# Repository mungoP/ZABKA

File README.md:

# Ż.A.B.K.A.

**Zero-moment Assisted Bipedal Kinetic Android**

ŻABKA ("little frog" in Polish) is a DIY 3D-printed humanoid robot. The current focus is the legs.

## Planned Specs

- **Height:** 3-4 ft
- **Legs:** 6 DoF each (3 hip, 1 knee, 2 ankle), 12 DoF total
- **Actuators:** Integrated motors with built-in drivers, controlled over CAN
- **Structure:** PETG, 4 walls, 10-20% infill
- **Power:** 48V Li-ion battery
- **Estimated weight:** 14-18 kg without arms

## Status

Early planning: selecting motors and finalizing the leg design.

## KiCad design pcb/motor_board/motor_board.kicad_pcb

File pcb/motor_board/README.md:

# Motor Board Planned Components

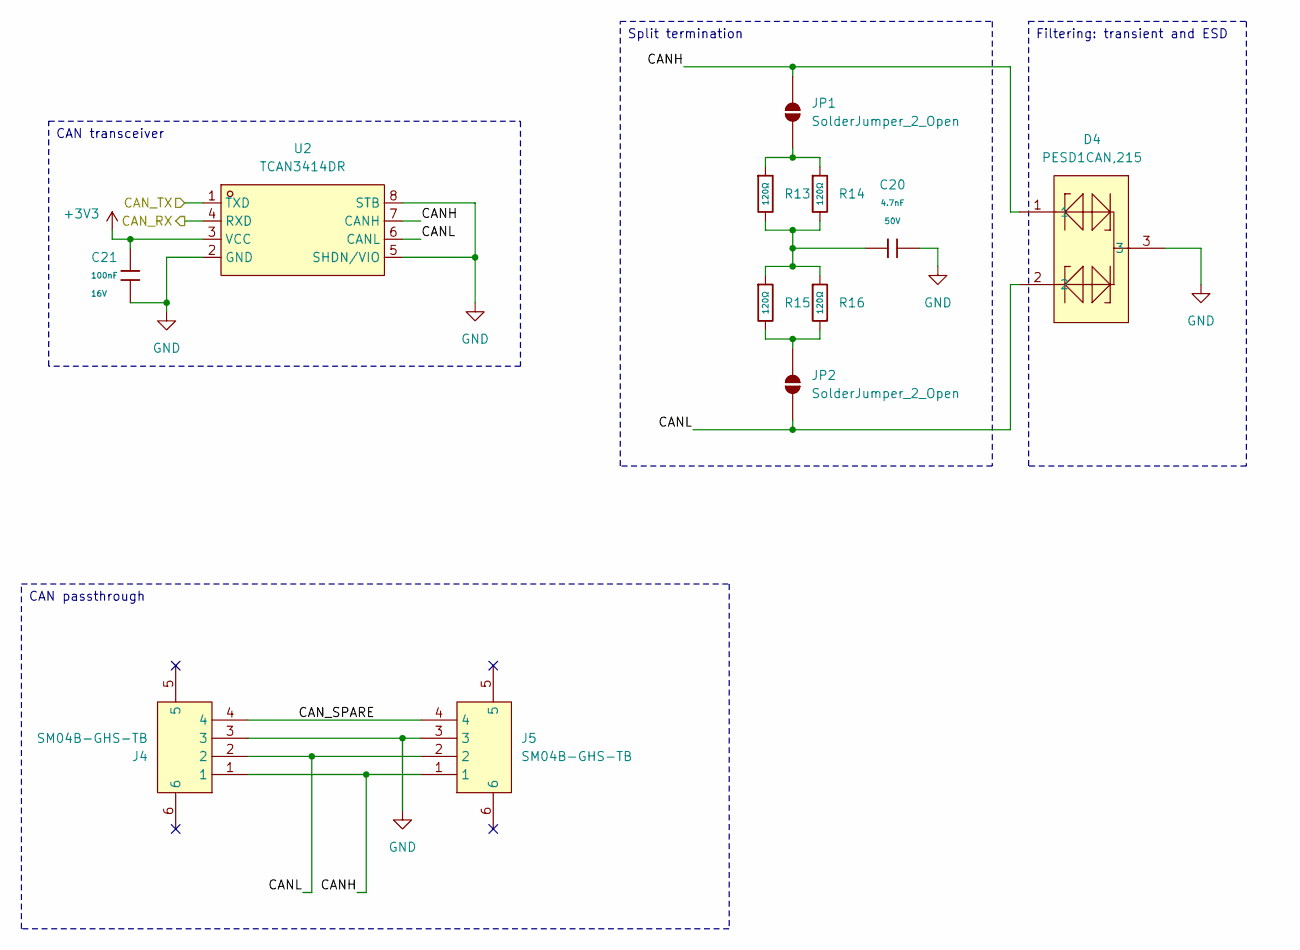
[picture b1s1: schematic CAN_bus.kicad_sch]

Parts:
C20: 4.7nF; C_0402; Voltage Rated 50V; Tolerance ±10%; Part 0402B472K500NT; LCSC C1538
C21: 100nF; C_0402; Voltage Rated 16V; Tolerance ±10%; Part CL05B104KO5NNNC; LCSC C1525
D4: PESD1CAN,215; SOT-23_L2.9-W1.3-P1.90-LS2.4-BR; MPN PESD1CAN,215; LCSC Part C15771
J4, J5: SM04B-GHS-TB; CONN-SMD_4P-P1.25_SM04B-GHS-TB-LF-SN; MPN SM04B-GHS-TB(LF)(SN); LCSC Part C189895
JP1, JP2: SolderJumper_2_Open; SolderJumper-2_P1.3mm_Open_Pad1.0x1.5mm
R13, R14, R15, R16: 120Ω; R_0402; Overload Voltage (Max) 50V; Tolerance ±1%; Part 0402WGF1200TCE; LCSC C25079
U2: TCAN3414DR; SOIC-8_L4.9-W3.9-P1.27-LS6.0-BL; MPN TCAN3414DR; LCSC Part C22396693

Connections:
+3V3: C21.1, U2.3 (VCC); also elsewhere on the board
/CAN bus/CANH: D4.1, J4.1, J5.1, JP1.2 (B), U2.7 (CANH)
/CAN bus/CANL: D4.2, J4.2, J5.2, JP2.1 (A), U2.6 (CANL)
/CAN bus/CAN_RX: U2.4 (RXD); also elsewhere on the board
/CAN bus/CAN_SPARE: J4.4, J5.4
/CAN bus/CAN_TX: U2.1 (TXD); also elsewhere on the board
GND: C20.2, C21.2, D4.3, J4.3, J5.3, U2.2 (GND), U2.5 (SHDN/VIO), U2.8 (STB); also elsewhere on the board
unnamed: C20.1, R13.2, R14.2, R15.1, R16.1
unnamed: JP1.1 (A), R13.1, R14.1
unnamed: JP2.2 (B), R15.2, R16.2

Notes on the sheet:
Split termination
CAN transceiver
CAN passthrough
Filtering: transient and ESD

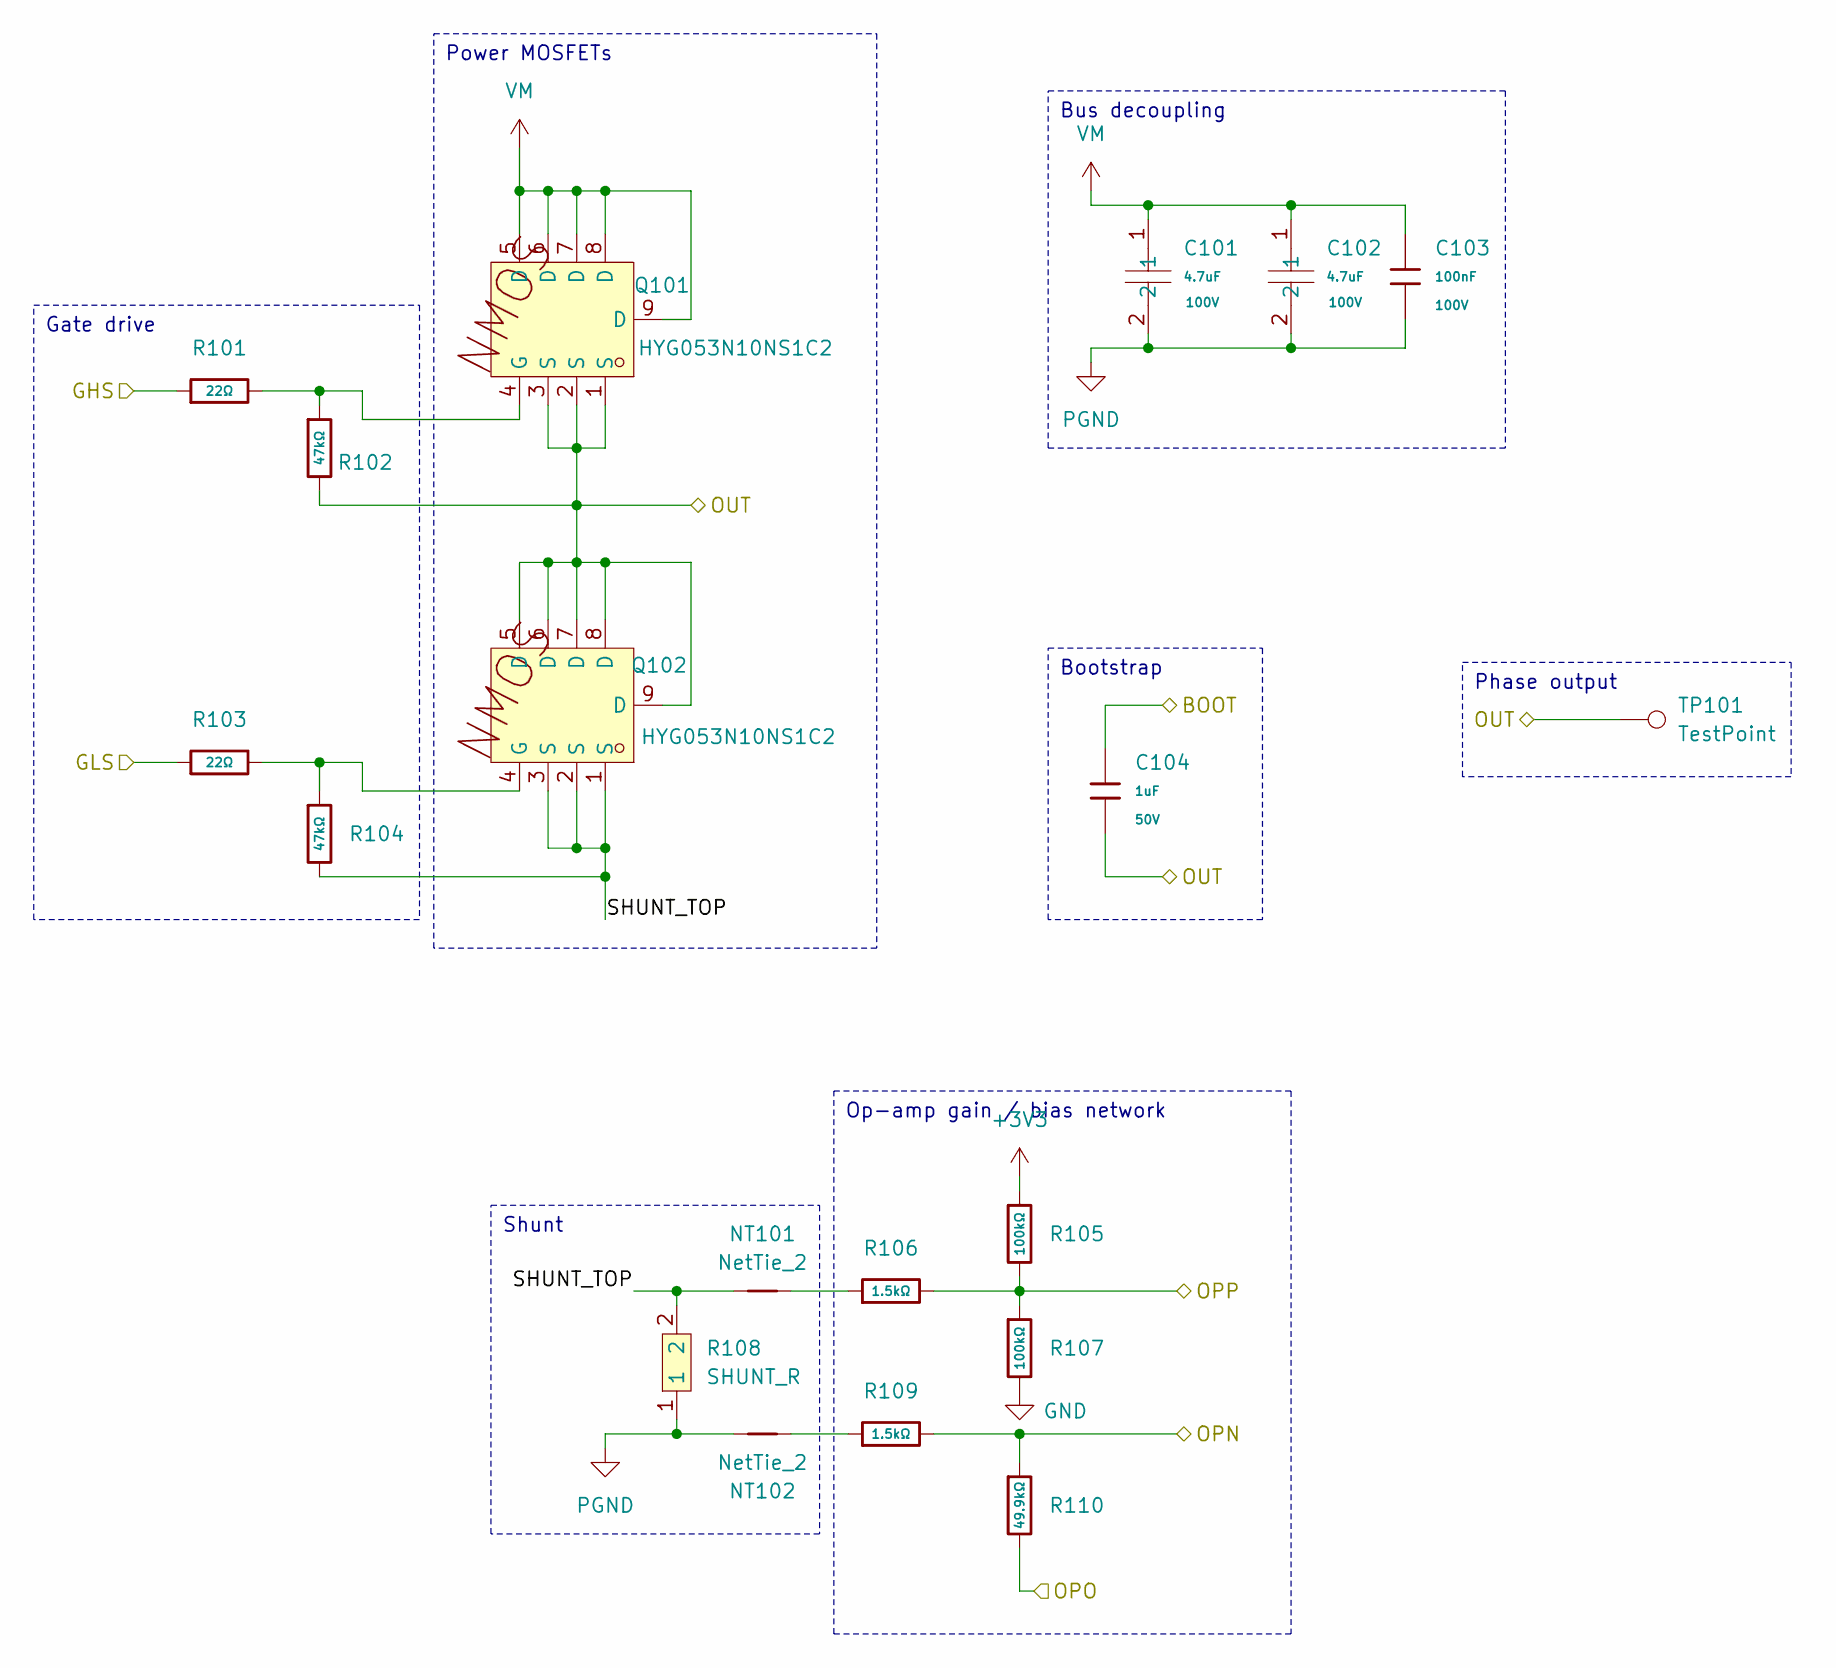
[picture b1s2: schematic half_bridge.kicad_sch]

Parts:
C101, C102: 4.7uF; C1210; MPN C1210X475K101T; LCSC Part C337978
C103: 100nF; C_0805; Voltage Rated 100V; Tolerance ±10%; Part CL21B104KCFNNNE; LCSC C28233
C104: 1uF; C_0603; Voltage Rated 50V; Tolerance ±10%; Part CL10A105KB8NNNC; LCSC C15849
NT101, NT102: NetTie_2; NetTie-2_SMD_Pad0.5mm
Q101, Q102: HYG053N10NS1C2; PDFN-8_L5.8-W5.0-P1.27-LS6.2-BL; MPN HYG053N10NS1C2; LCSC Part C2986239
R101, R103: 22Ω; R_0603; Overload Voltage (Max) 75V; Tolerance ±1%; Part 0603WAF220JT5E; LCSC C23345
R102, R104: 47kΩ; R_0402; Overload Voltage (Max) 50V; Tolerance ±1%; Part 0402WGF4702TCE; LCSC C25792
R105, R107: 100kΩ; R_0603; Overload Voltage (Max) 75V; Tolerance ±1%; Part 0603WAF1003T5E; LCSC C25803
R106, R109: 1.5kΩ; R_0603; Overload Voltage (Max) 75V; Tolerance ±1%; Part 0603WAF1501T5E; LCSC C22843
R108: SHUNT_R; RES-SMD_L6.4-W3.2_LR2512D-3W-1MR; MPN LR2512D-3W-1mR-1%; LCSC Part C500734
R110: 49.9kΩ; R_0402; Overload Voltage (Max) 50V; Tolerance ±1%; Part 0402WGF4992TCE; LCSC C25897
TP101: TestPoint; TestPoint_Pad_4.0x4.0mm

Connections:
+3V3: R105.1; also elsewhere on the board
/Controller/BOOT1: C104.1; also elsewhere on the board
/Controller/GHS1: R101.1; also elsewhere on the board
/Controller/GLS1: R103.1; also elsewhere on the board
/Controller/OPN1: R109.2, R110.1; also elsewhere on the board
/Controller/OPO1: R110.2; also elsewhere on the board
/Controller/OPP1: R105.2, R106.2, R107.1; also elsewhere on the board
/Controller/OUT1: C104.2, Q101.1 (S), Q101.2 (S), Q101.3 (S), Q102.5 (D), Q102.6 (D), Q102.7 (D), Q102.8 (D), Q102.9 (D), R102.2, TP101.1 (1_1); also elsewhere on the board
/Half bridge - U/SHUNT_TOP: NT101.1, Q102.1 (S), Q102.2 (S), Q102.3 (S), R104.2, R108.2
GND: R107.2; also elsewhere on the board
unnamed: NT101.2, R106.1
unnamed: NT102.1, R109.1
unnamed: Q101.4 (G), R101.2, R102.1
unnamed: Q102.4 (G), R103.2, R104.1
PGND: C101.2, C102.2, C103.2, NT102.2, R108.1; also elsewhere on the board
VM: C101.1, C102.1, C103.1, Q101.5 (D), Q101.6 (D), Q101.7 (D), Q101.8 (D), Q101.9 (D); also elsewhere on the board

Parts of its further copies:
C201, C202, C301, C302: 4.7uF; C1210; MPN C1210X475K101T; LCSC Part C337978
C203, C303: 100nF; C_0805; Voltage Rated 100V; Tolerance ±10%; Part CL21B104KCFNNNE; LCSC C28233
C204, C304: 1uF; C_0603; Voltage Rated 50V; Tolerance ±10%; Part CL10A105KB8NNNC; LCSC C15849
NT201, NT202, NT301, NT302: NetTie_2; NetTie-2_SMD_Pad0.5mm
Q201, Q202, Q301, Q302: HYG053N10NS1C2; PDFN-8_L5.8-W5.0-P1.27-LS6.2-BL; MPN HYG053N10NS1C2; LCSC Part C2986239
R201, R203, R301, R303: 22Ω; R_0603; Overload Voltage (Max) 75V; Tolerance ±1%; Part 0603WAF220JT5E; LCSC C23345
R202, R204, R302, R304: 47kΩ; R_0402; Overload Voltage (Max) 50V; Tolerance ±1%; Part 0402WGF4702TCE; LCSC C25792
R205, R207, R305, R307: 100kΩ; R_0603; Overload Voltage (Max) 75V; Tolerance ±1%; Part 0603WAF1003T5E; LCSC C25803
R206, R209, R306, R309: 1.5kΩ; R_0603; Overload Voltage (Max) 75V; Tolerance ±1%; Part 0603WAF1501T5E; LCSC C22843
R208, R308: SHUNT_R; RES-SMD_L6.4-W3.2_LR2512D-3W-1MR; MPN LR2512D-3W-1mR-1%; LCSC Part C500734
R210, R310: 49.9kΩ; R_0402; Overload Voltage (Max) 50V; Tolerance ±1%; Part 0402WGF4992TCE; LCSC C25897
TP201, TP301: TestPoint; TestPoint_Pad_4.0x4.0mm

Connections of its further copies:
+3V3: R205.1, R305.1; also elsewhere on the board
/Controller/BOOT2: C204.1; also elsewhere on the board
/Controller/BOOT3: C304.1; also elsewhere on the board
/Controller/GHS2: R201.1; also elsewhere on the board
/Controller/GHS3: R301.1; also elsewhere on the board
/Controller/GLS2: R203.1; also elsewhere on the board
/Controller/GLS3: R303.1; also elsewhere on the board
/Controller/OPN2: R209.2, R210.1; also elsewhere on the board
/Controller/OPN3: R309.2, R310.1; also elsewhere on the board
/Controller/OPO2: R210.2; also elsewhere on the board
/Controller/OPO3: R310.2; also elsewhere on the board
/Controller/OPP2: R205.2, R206.2, R207.1; also elsewhere on the board
/Controller/OPP3: R305.2, R306.2, R307.1; also elsewhere on the board
/Controller/OUT2: C204.2, Q201.1 (S), Q201.2 (S), Q201.3 (S), Q202.5 (D), Q202.6 (D), Q202.7 (D), Q202.8 (D), Q202.9 (D), R202.2, TP201.1 (1_1); also elsewhere on the board
/Controller/OUT3: C304.2, Q301.1 (S), Q301.2 (S), Q301.3 (S), Q302.5 (D), Q302.6 (D), Q302.7 (D), Q302.8 (D), Q302.9 (D), R302.2, TP301.1 (1_1); also elsewhere on the board
/Half bridge - V/SHUNT_TOP: NT201.1, Q202.1 (S), Q202.2 (S), Q202.3 (S), R204.2, R208.2
/Half bridge - W/SHUNT_TOP: NT301.1, Q302.1 (S), Q302.2 (S), Q302.3 (S), R304.2, R308.2
GND: R207.2, R307.2; also elsewhere on the board
unnamed: NT201.2, R206.1
unnamed: NT202.1, R209.1
unnamed: NT301.2, R306.1
unnamed: NT302.1, R309.1
unnamed: Q201.4 (G), R201.2, R202.1
unnamed: Q202.4 (G), R203.2, R204.1
unnamed: Q301.4 (G), R301.2, R302.1
unnamed: Q302.4 (G), R303.2, R304.1
PGND: C201.2, C202.2, C203.2, C301.2, C302.2, C303.2, NT202.2, NT302.2, R208.1, R308.1; also elsewhere on the board
VM: C201.1, C202.1, C203.1, C301.1, C302.1, C303.1, Q201.5 (D), Q201.6 (D), Q201.7 (D), Q201.8 (D), Q201.9 (D), Q301.5 (D), Q301.6 (D), Q301.7 (D), Q301.8 (D), Q301.9 (D); also elsewhere on the board

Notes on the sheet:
Bootstrap
Gate drive
Shunt
Bus decoupling
Power MOSFETs
Op-amp gain / bias network
Phase output

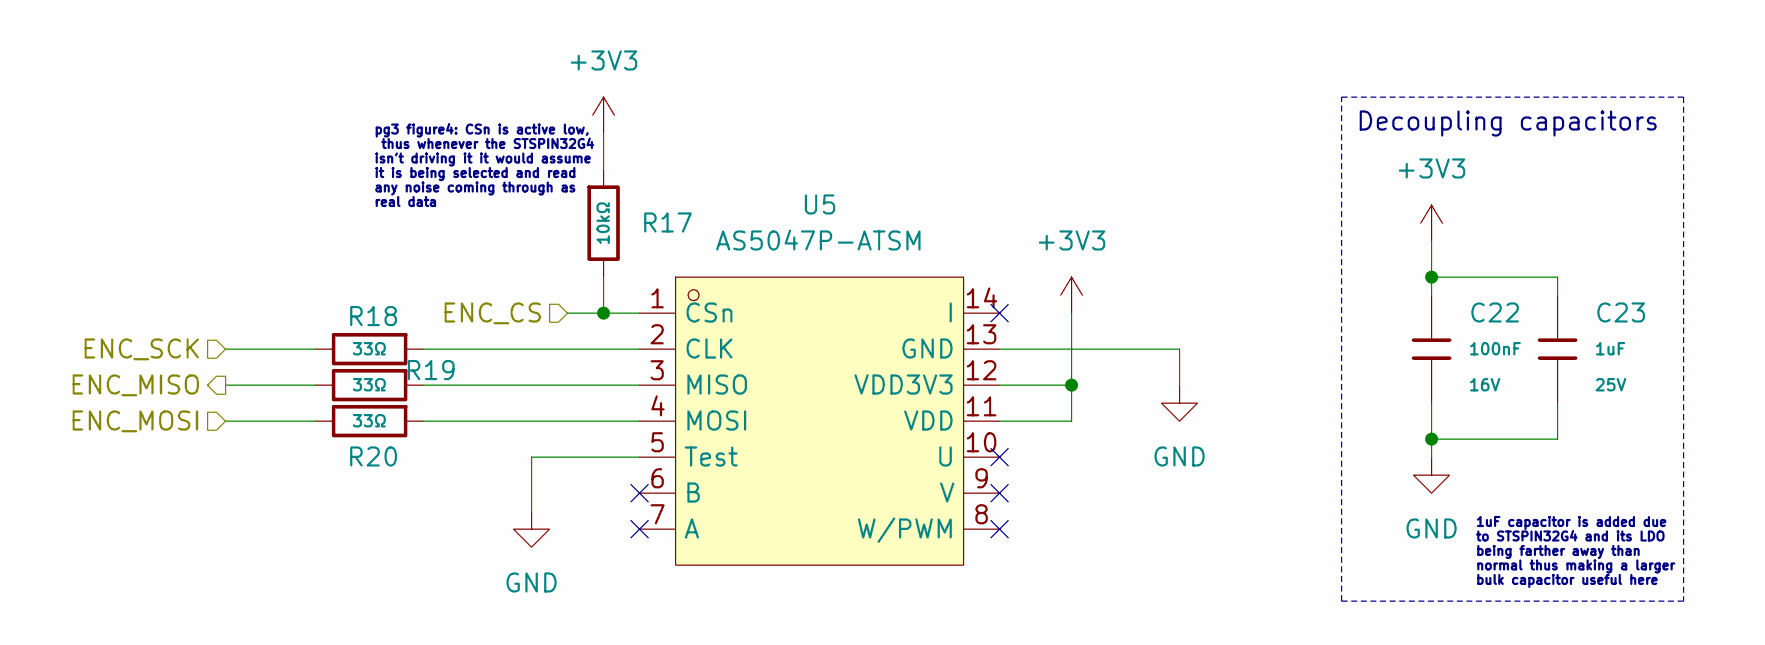
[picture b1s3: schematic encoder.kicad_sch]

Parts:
C22: 100nF; C_0402; Voltage Rated 16V; Tolerance ±10%; Part CL05B104KO5NNNC; LCSC C1525
C23: 1uF; C_0402; Voltage Rated 25V; Tolerance ±10%; Part CL05A105KA5NQNC; LCSC C52923
R17: 10kΩ; R_0402; Overload Voltage (Max) 50V; Tolerance ±1%; Part 0402WGF1002TCE; LCSC C25744
R18, R19, R20: 33Ω; R_0402; Overload Voltage (Max) 50V; Tolerance ±1%; Part 0402WGF330JTCE; LCSC C25105
U5: AS5047P-ATSM; TSSOP-14_L5.0-W4.4-P0.65-LS6.4-BL; MPN AS5047P-ATSM; LCSC Part C962063

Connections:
+3V3: C22.1, C23.1, R17.1, U5.11 (VDD), U5.12 (VDD3V3); also elsewhere on the board
/Controller/ENC_CS: R17.2, U5.1 (CSn); also elsewhere on the board
/Controller/ENC_MISO: R19.2; also elsewhere on the board
/Controller/ENC_MOSI: R20.2; also elsewhere on the board
/Controller/ENC_SCK: R18.2; also elsewhere on the board
GND: C22.2, C23.2, U5.5 (Test), U5.13 (GND); also elsewhere on the board
unnamed: R18.1, U5.2 (CLK)
unnamed: R19.1, U5.3 (MISO)
unnamed: R20.1, U5.4 (MOSI)

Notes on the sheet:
pg3 figure4: CSn is active low, thus whenever the STSPIN32G4 isn't driving it it would assume it is being selected and read any noise coming through as real data
1uF capacitor is added due to STSPIN32G4 and its LDO being farther away than normal thus making a larger bulk capacitor useful here
Decoupling capacitors

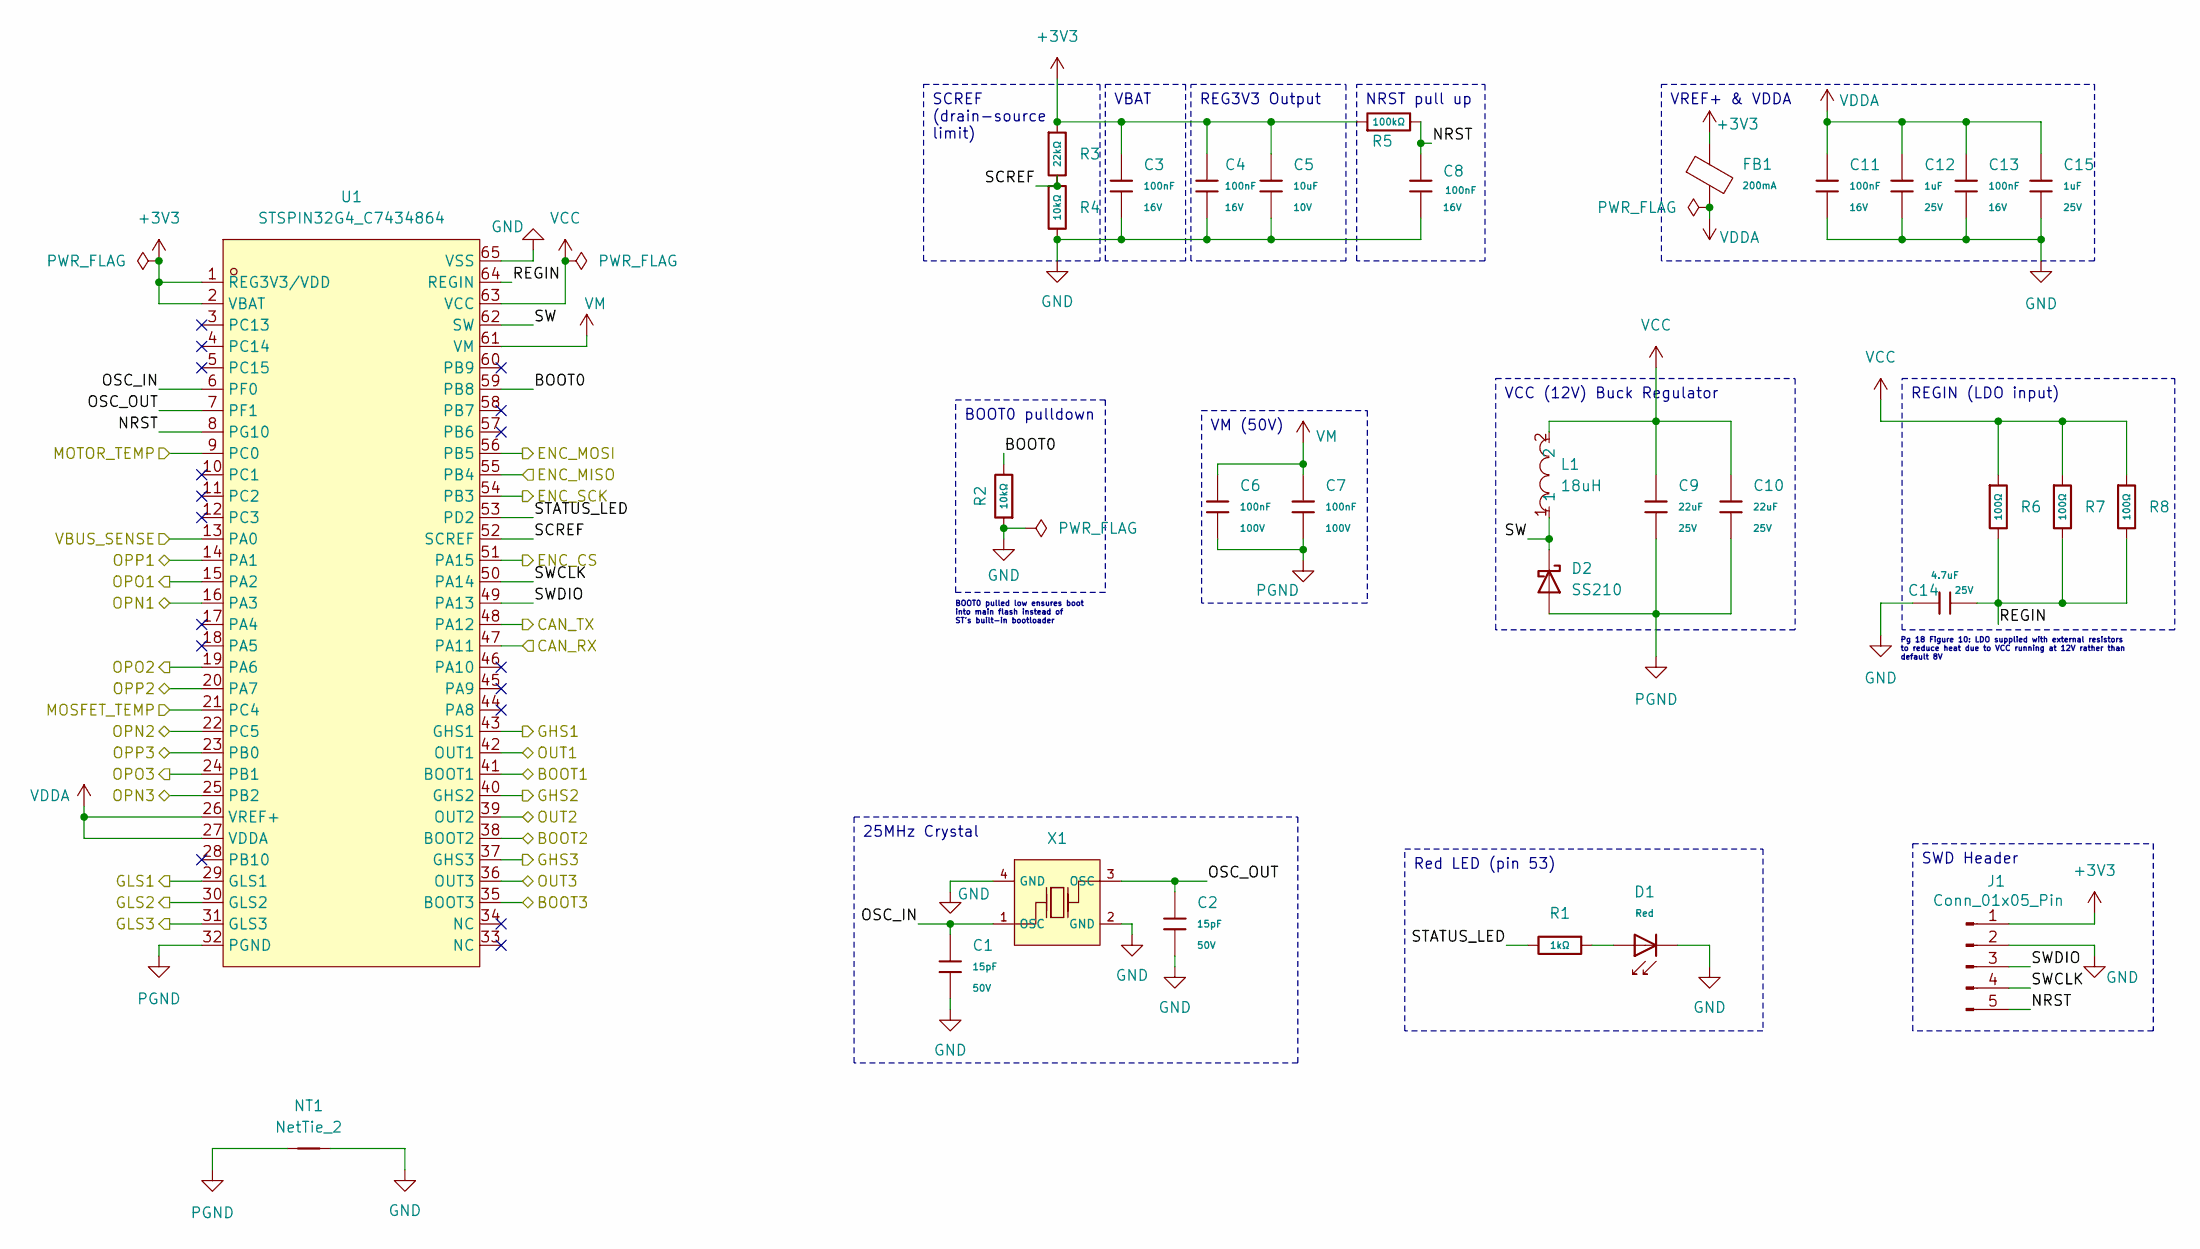
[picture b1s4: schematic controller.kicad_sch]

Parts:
C1, C2: 15pF; C_0402; Voltage Rated 50V; Tolerance ±5%; Part 0402CG150J500NT; LCSC C1548
C3, C4, C8, C11, C13: 100nF; C_0402; Voltage Rated 16V; Tolerance ±10%; Part CL05B104KO5NNNC; LCSC C1525
C5: 10uF; C_0603; Voltage Rated 10V; Tolerance ±10%; Part CL10A106KP8NNNC; LCSC C19702
C6, C7: 100nF; C_0805; Voltage Rated 100V; Tolerance ±10%; Part CL21B104KCFNNNE; LCSC C28233
C9, C10: 22uF; C_1206; Voltage Rated 25V; Tolerance ±10%; Part CL31A226KAHNNNE; LCSC C12891
C12, C15: 1uF; C_0402; Voltage Rated 25V; Tolerance ±10%; Part CL05A105KA5NQNC; LCSC C52923
C14: 4.7uF; C_0805; Voltage Rated 25V; Tolerance ±10%; Part CL21A475KAQNNNE; LCSC C1779
D1: Red; D_0603; Part KT-0603R; LCSC C2286
D2: SS210; D_SMA
FB1: FB_0603; Current Rating 200mA; Tolerance ±25%; Part GZ1608D601TF; LCSC C1002
J1: Conn_01x05_Pin; PinHeader_1x05_P2.54mm_Horizontal
L1: 18uH; IND-SMD_L6.0-W6.0_FNR60XXS; MPN FNR6020S180MT; LCSC Part C168016
NT1: NetTie_2; NetTie-2_SMD_Pad0.5mm
R1: 1kΩ; R_0402; Overload Voltage (Max) 50V; Tolerance ±1%; Part 0402WGF1001TCE; LCSC C11702
R2, R4: 10kΩ; R_0402; Overload Voltage (Max) 50V; Tolerance ±1%; Part 0402WGF1002TCE; LCSC C25744
R3: 22kΩ; R_0402; Overload Voltage (Max) 50V; Tolerance ±1%; Part 0402WGF2202TCE; LCSC C25768
R5: 100kΩ; R_0402; Overload Voltage (Max) 50V; Tolerance ±1%; Part 0402WGF1003TCE; LCSC C25741
R6, R7, R8: 100Ω; R_1206; Overload Voltage (Max) 200V; Tolerance ±1%; Part 1206W4F1000T5E; LCSC C17901
U1: STSPIN32G4_C7434864; VFQFPN-64_L9.0-W9.0-P0.50-TL-EP4.0; MPN STSPIN32G4; LCSC Part C7434864
X1: X322525MOB4SI; OSC-SMD_4P-L3.2-W2.5-BL; Frequency Tolerance ±10ppm; Part X322525MOB4SI; LCSC C9006

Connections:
+3V3: C3.1, C4.1, C5.1, FB1.1, J1.1, R3.1, R5.1, U1.1 (REG3V3/VDD), U1.2 (VBAT); also elsewhere on the board
/CAN bus/CAN_RX: U1.47 (PA11); also elsewhere on the board
/CAN bus/CAN_TX: U1.48 (PA12); also elsewhere on the board
/Controller/BOOT0: R2.2, U1.59 (PB8)
/Controller/BOOT1: U1.41 (BOOT1); also elsewhere on the board
/Controller/BOOT2: U1.38 (BOOT2); also elsewhere on the board
/Controller/BOOT3: U1.35 (BOOT3); also elsewhere on the board
/Controller/ENC_CS: U1.51 (PA15); also elsewhere on the board
/Controller/ENC_MISO: U1.55 (PB4); also elsewhere on the board
/Controller/ENC_MOSI: U1.56 (PB5); also elsewhere on the board
/Controller/ENC_SCK: U1.54 (PB3); also elsewhere on the board
/Controller/GHS1: U1.43 (GHS1); also elsewhere on the board
/Controller/GHS2: U1.40 (GHS2); also elsewhere on the board
/Controller/GHS3: U1.37 (GHS3); also elsewhere on the board
/Controller/GLS1: U1.29 (GLS1); also elsewhere on the board
/Controller/GLS2: U1.30 (GLS2); also elsewhere on the board
/Controller/GLS3: U1.31 (GLS3); also elsewhere on the board
/Controller/MOSFET_TEMP: U1.21 (PC4); also elsewhere on the board
/Controller/MOTOR_TEMP: U1.9 (PC0); also elsewhere on the board
/Controller/NRST: C8.1, J1.5, R5.2, U1.8 (PG10)
/Controller/OPN1: U1.16 (PA3); also elsewhere on the board
/Controller/OPN2: U1.22 (PC5); also elsewhere on the board
/Controller/OPN3: U1.25 (PB2); also elsewhere on the board
/Controller/OPO1: U1.15 (PA2); also elsewhere on the board
/Controller/OPO2: U1.19 (PA6); also elsewhere on the board
/Controller/OPO3: U1.24 (PB1); also elsewhere on the board
/Controller/OPP1: U1.14 (PA1); also elsewhere on the board
/Controller/OPP2: U1.20 (PA7); also elsewhere on the board
/Controller/OPP3: U1.23 (PB0); also elsewhere on the board
/Controller/OSC_IN: C1.1, U1.6 (PF0), X1.1 (OSC)
/Controller/OSC_OUT: C2.1, U1.7 (PF1), X1.3 (OSC)
/Controller/OUT1: U1.42 (OUT1); also elsewhere on the board
/Controller/OUT2: U1.39 (OUT2); also elsewhere on the board
/Controller/OUT3: U1.36 (OUT3); also elsewhere on the board
/Controller/REGIN: C14.2, R6.2, R7.2, R8.2, U1.64 (REGIN)
/Controller/SCREF: R3.2, R4.1, U1.52 (SCREF)
/Controller/STATUS_LED: R1.2, U1.53 (PD2)
/Controller/SW: D2.1 (K), L1.1, U1.62 (SW)
/Controller/SWCLK: J1.4, U1.50 (PA14)
/Controller/SWDIO: J1.3, U1.49 (PA13)
/Controller/VBUS_SENSE: U1.13 (PA0); also elsewhere on the board
GND: C1.2, C2.2, C3.2, C4.2, C5.2, C8.2, C11.2, C12.2, C13.2, C14.1, C15.2, D1.1, J1.2, NT1.2, R2.1, R4.2, U1.65 (VSS), X1.2 (GND), X1.4 (GND); also elsewhere on the board
unnamed: D1.2, R1.1
PGND: C6.2, C7.2, C9.2, C10.2, D2.2 (A), NT1.1, U1.32 (PGND); also elsewhere on the board
VCC: C9.1, C10.1, L1.2, R6.1, R7.1, R8.1, U1.63 (VCC)
VDDA: C11.1, C12.1, C13.1, C15.1, FB1.2, U1.26 (VREF+), U1.27 (VDDA)
VM: C6.1, C7.1, U1.61 (VM); also elsewhere on the board

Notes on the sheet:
Pg 18 Figure 10: LDO supplied with external resistors to reduce heat due to VCC running at 12V rather than default 8V
BOOT0 pulled low ensures boot into main flash instead of ST's built-in bootloader
Red LED (pin 53)
BOOT0 pulldown
SCREF (drain-source limit)
25MHz Crystal
NRST pull up
REG3V3 Output
VM (50V)
VCC (12V) Buck Regulator
VREF+ & VDDA
SWD Header
VBAT
REGIN (LDO input)

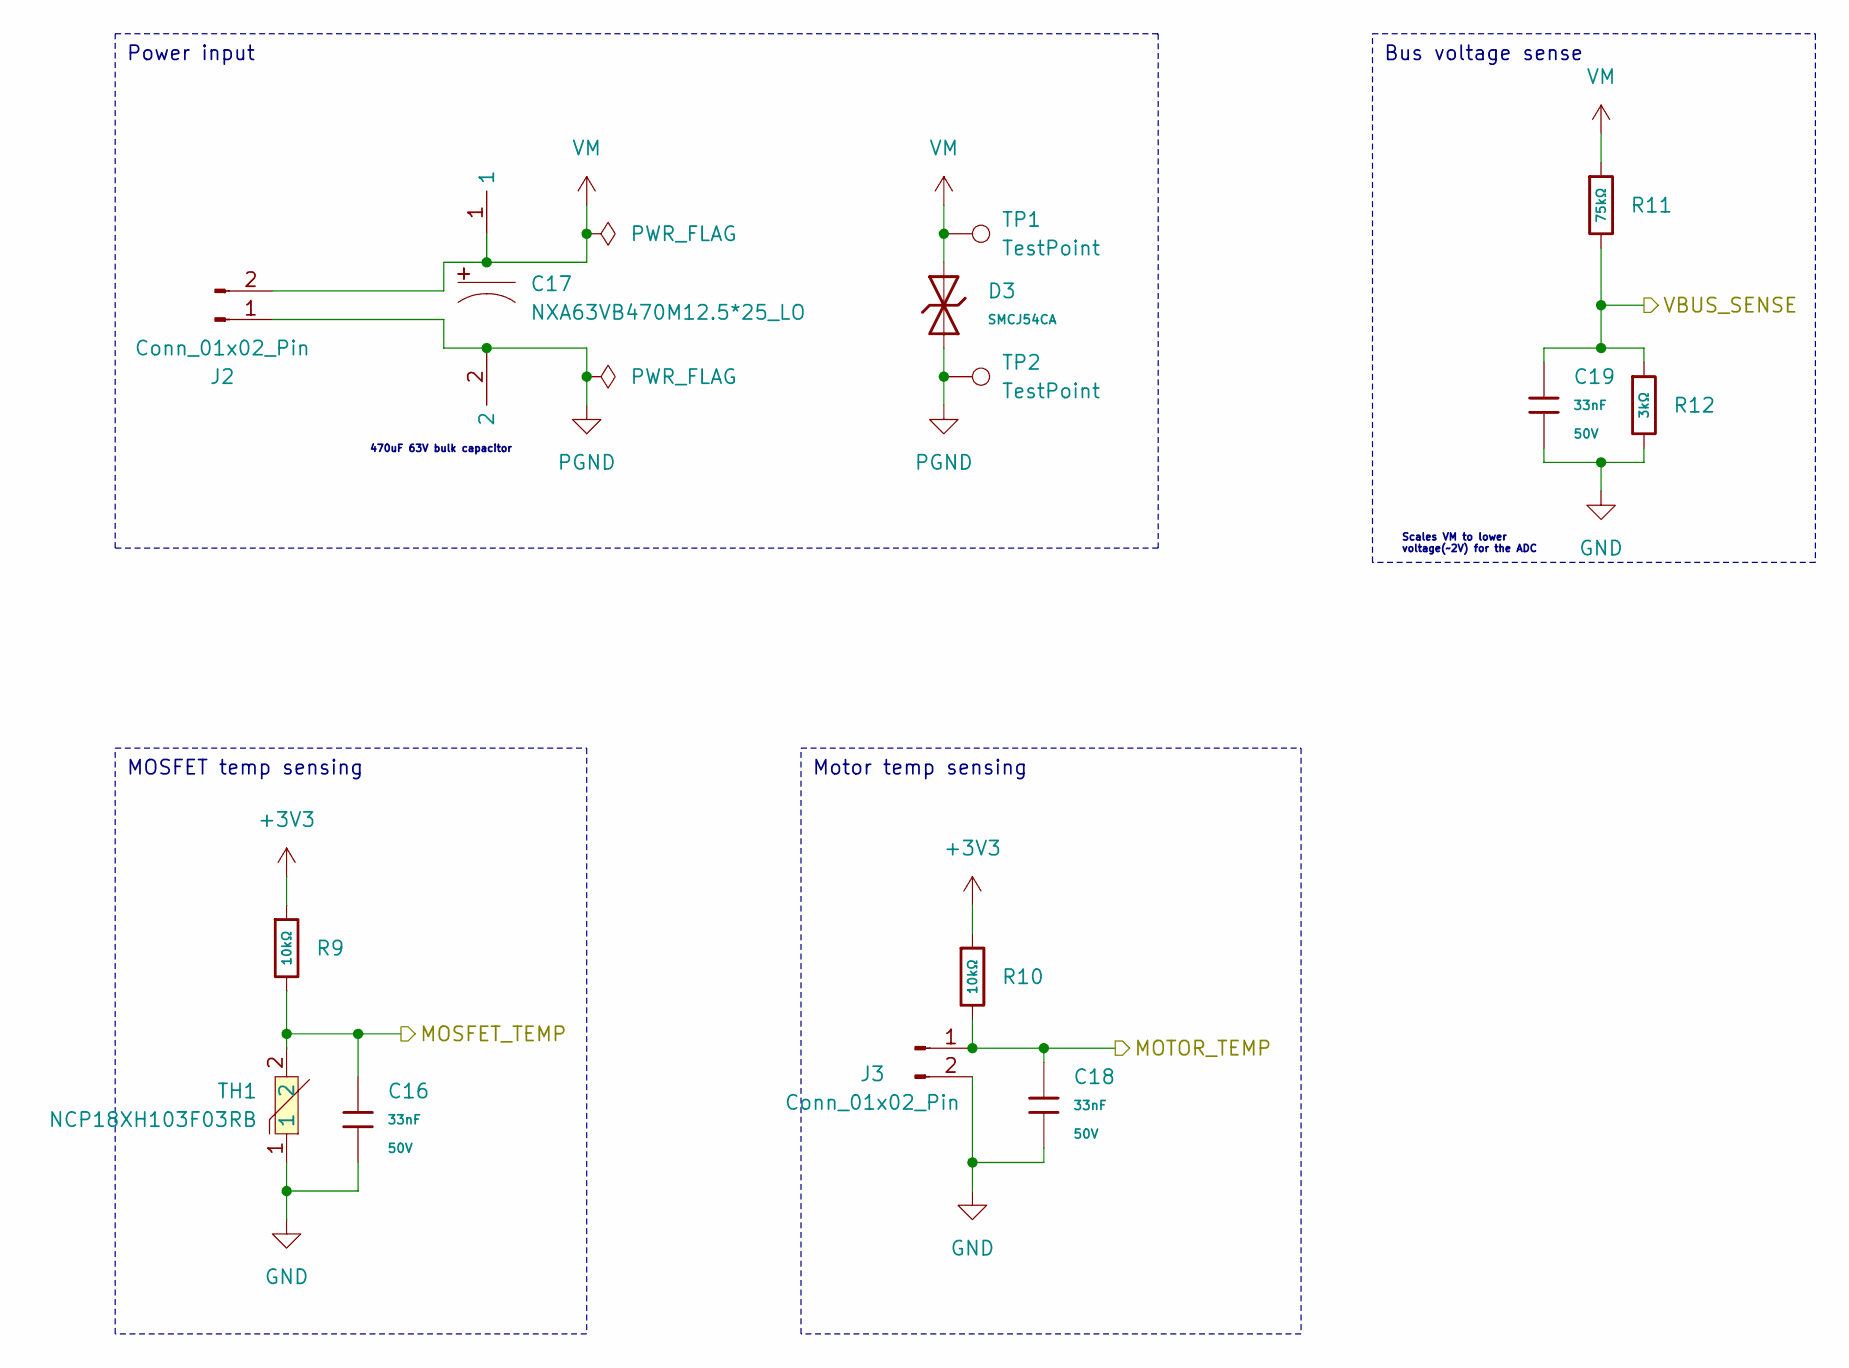
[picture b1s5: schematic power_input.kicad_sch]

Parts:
C16, C18, C19: 33nF; C_0603; Voltage Rated 50V; Tolerance ±10%; Part CL10B333KB8NNNC; LCSC C21117
C17: NXA63VB470M12.5*25_LO; CAP-TH_BD12.5-P5.00-D0.6-FD; MPN NXA63V470M12.5*25 LO; LCSC Part C371297
D3: SMCJ54CA; D_SMC; Clamping Voltage 87.1V; Voltage - Breakdown 66.3V; Part SMCJ54CA; LCSC C41411761
J2: Conn_01x02_Pin; AMASS_XT30PW-M_1x02_P2.50mm_Horizontal
J3: Conn_01x02_Pin; JST_GH_SM02B-GHS-TB_1x02-1MP_P1.25mm_Horizontal
R9, R10: 10kΩ; R_0402; Overload Voltage (Max) 50V; Tolerance ±1%; Part 0402WGF1002TCE; LCSC C25744
R11: 75kΩ; R_0603; Overload Voltage (Max) 75V; Tolerance ±1%; Part 0603WAF7502T5E; LCSC C23242
R12: 3kΩ; R_0603; Overload Voltage (Max) 75V; Tolerance ±1%; Part 0603WAF3001T5E; LCSC C4211
TH1: NCP18XH103F03RB; R0603; MPN NCP18XH103F03RB; LCSC Part C13564
TP1, TP2: TestPoint; TestPoint_Pad_1.5x1.5mm

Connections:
+3V3: R9.1, R10.1; also elsewhere on the board
/Controller/MOSFET_TEMP: C16.1, R9.2, TH1.2; also elsewhere on the board
/Controller/MOTOR_TEMP: C18.1, J3.1, R10.2; also elsewhere on the board
/Controller/VBUS_SENSE: C19.1, R11.2, R12.1; also elsewhere on the board
GND: C16.2, C18.2, C19.2, J3.2, R12.2, TH1.1; also elsewhere on the board
PGND: C17.2, D3.1, J2.1, TP2.1 (1_1); also elsewhere on the board
VM: C17.1, D3.2, J2.2, R11.1, TP1.1 (1_1); also elsewhere on the board

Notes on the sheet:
470uF 63V bulk capacitor
Scales VM to lower voltage(~2V) for the ADC
Motor temp sensing
MOSFET temp sensing
Bus voltage sense
Power input

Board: 4 copper layers, 121 parts (3 on the bottom side), 71 nets, no tracks yet.
